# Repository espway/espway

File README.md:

# ESPway
A segway-like balancing two-wheel robot built on ESP8266. It is controlled over WiFi via a HTML/JS GUI and a WebSocket. This is a work in progress. The firmware is meant to run on a WEMOS D1 mini or a similar board.

*NOTE for existing users*: the [Arduino version](https://github.com/flannelhead/espway/tree/arduino) of this code is deprecated and will *not* receive the newest improvements from the main branch. However, the Arduino branch will remain in this repo. If you'd like to have something improved or fixed there, please open an issue or preferably a pull request.

## Getting started
The firmware is built on the [esp-open-rtos](https://github.com/SuperHouse/esp-open-rtos) project which is included as a submodule in this repo.

For building the firmware, a Linux host is recommended. For other platforms, there is a [Docker image](https://hub.docker.com/r/flannelhead/espway-toolchain/) one can use. The `docker-run` script in this repository contains the command that's required to download the image and run commands in the container. It should work fine on macOS hosts. For Windows hosts, I still recommend installing Linux in a virtual machine and installing the tools there.

### Installing the tools and building

*NOTE*: if you intend to use Docker, you only have to install `esptool`, `git` and `make` on your host. Please see below for further Docker instructions.

### Using the Docker image

First, [install Docker](https://www.docker.com/community-edition).

Building the firmware using the supplied Docker image is easy. Instead of running `make parallel`, just run `./docker-run make parallel` in the root folder of the repo. The command supplied to the script will be run in the Docker container, and the image will be automatically downloaded.

Flashing the image differs, though, and for this you'll need `make` on your host. Instead of
```
make flash ESPPORT=/dev/ttyUSBx
```
(`/dev/ttyUSBx` being the ESP's serial port) run
```
make flash-only ESPPORT=/dev/ttyUSBx
```
in your host shell. The separate `flash-only` target is needed because the `flash` target would try to build the firmware. In the future, it is intended to provide a separate Python script for flashing, lifting the need for `make` on host.

*TODO*: `docker-compose` configuration file for even easier usage

### Installing the tools manually (not recommended, not guaranteed to work)

**WARNING**: As of currently, the compiler installed by this method seems to have issues compiling the code. Thus this method is not recommended. Please see above for the Docker-based toolchain instead.

Install these packages:
* `git` (from your package manager)
* `xtensa-lx106-elf` toolchain. You can use `esp-open-sdk` to build it, see the [instructions](https://github.com/SuperHouse/esp-open-rtos/#quick-start) in the esp-open-rtos repo.
* `esptool` (`pip install -U esptool`). Please do not use the outdated version pulled by `esp-open-sdk`.
* `tcc`, `nodejs` and `npm` are currently required due to the frontend code, although I'm investigating how to relax this dependency.

Clone this repo (recursive cloning to get also `esp-open-rtos` and its submodules):
```
git clone --recursive https://github.com/flannelhead/espway.git
```
Enter the directory and build the firmware:
```
make parallel
```
The `parallel` target does a clean build with 5 parallel worker threads to make it faster.

Plug your ESP8266 module in via USB and flash the firmware:
```
make flash
```
The default port is `/dev/ttyUSB0`. If you need to change this, use
```
make flash ESPPORT=/dev/ttyUSBx
```

## Supported browsers
Please use the latest Firefox or Chrome if possible. The HTML/JS UI uses some
recent JavaScript features which might not be supported by older browsers. However if you encounter any issues on e.g. Safari, don't hesitate to file them in the issue tracker.

## Schematic & BOM

There is a PCB design and schematic in the `schematic` folder which has been tested and is ready to use. There, MPU6050 has been replaced by LSM6DS3 and L293D by DRV8835 for better performance.

Meanwhile, you can still build an ESPway using breakout boards available from the usual sources. A rough bill of materials for this is listed below:

* (not including PCB, connectors, wire etc. materials)
* WEMOS D1 Mini board
* GY-521 (MPU6050 breakout board)
* L293D motor driver IC
* 2x 6V 300rpm metal gear motor (search for "12ga 300rpm" or "n20 300rpm"), these should be $3-5 per piece
* 2x WS2812B neopixels for eyes and showing current state
* AMS1117 5V regulator
* 5x 100n ceramic capacitors
* 2x 1000u 10V electrolytic capacitor
* 470 ohm resistor
* 10 kohm resistor
* 680 kohm resistor

To use the old hardware config and schematic, you'll have to edit `src/espway_config.h` before compilation. See that file for notes.

See the `schematic-old` folder for the schematic. It is drawn with [KiCad](https://kicad.org/) and there's a [rendered PDF](https://github.com/flannelhead/espway/raw/master/schematic/espway.pdf) in the repo.

The new schematic in `schematic` folder uses components
from [kicad-ESP8266](https://github.com/jdunmire/kicad-ESP8266) by J. Dunmire,
licensed under CC-BY-SA 4.0. The schematic is also licensed under CC-BY-SA 4.0.

## Developing the frontend
The HTML/JS frontend uses [Webpack](https://webpack.github.io/) as the build system. You will need [NodeJS](https://nodejs.org/en/) and NPM (the package manager) to build the frontend pages. It does jobs like bundling the JavaScript modules together, minifying and transpiling the [ES2015](https://babeljs.io/learn-es2015/) code for older browsers, compiling [Riot tags](https://riot.js.org/), minifying/autoprefixing CSS etc.

After you've cloned this repo, run `npm install` in the root folder to install the package dependencies. There are two commands specified in `package.json` which run Webpack:

* `npm run serve` start a web server which serves the static HTML files in the `frontend/output` directory. It also watches for changes in the source files in `frontend/src` and automatically rebuilds and reloads them. Use this while hacking on the frontend. *TODO*: Currently this doesn't see changes to HTML files, though.
* `npm run build` produces a production build of the frontend JS/CSS bundles. Use this before uploading your work to the ESP8266.

## License and acknowledgements
The project is licensed under LGPLv3.

The project uses `esp-open-rtos` which is licensed under the BSD 3-clause license. It also has some components which have different licenses. Read more about them in the [`esp-open-rtos` README](https://github.com/SuperHouse/esp-open-rtos/blob/master/README.md).

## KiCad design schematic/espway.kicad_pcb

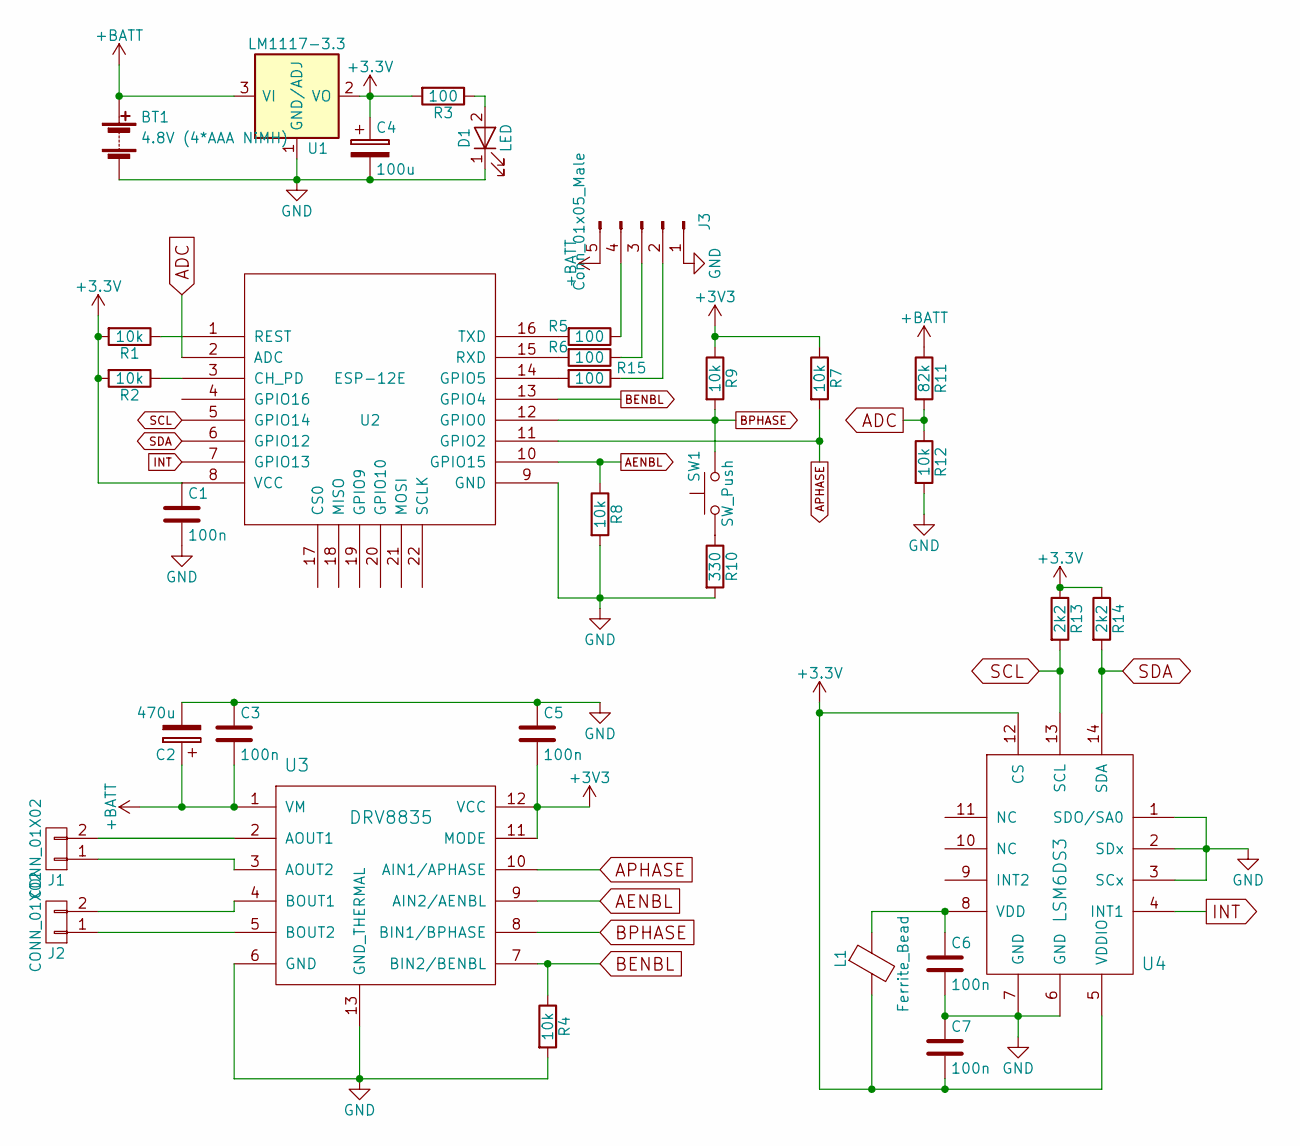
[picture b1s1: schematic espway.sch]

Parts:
BT1: 4.8V (4*AAA NiMH); WireConnection_1.20mmDrill
C1, C3, C5, C6, C7: 100n; C_0603
C2: 470u; CP_Elec_8x10
C4: 100u; CP_Elec_6.3x5.8
D1: LED; LED_0603
J1, J2: CONN_01X02; WireConnection_1.00mmDrill
J3: Conn_01x05_Male; Pin_Header_Angled_1x05_Pitch2.54mm
L1: Ferrite_Bead; L_0603
R1, R2, R4, R7, R8, R9, R12: 10k; R_0603
R3, R5, R6, R15: 100; R_0603
R10: 330; R_0603
R11: 82k; R_0603
R13, R14: 2k2; R_0603
SW1: SW_Push; SW_SPST_KMR2
U1: LM1117-3.3; SOT-223
U2: ESP-12E; ESP-12E_SMD
U3: DRV8835; WSON-12-1EP_3x2mm_Pitch0.5mm_ThermalVias
U4: LSM6DS3; Bosch_LGA-14_3x2.5mm_Pitch0.5mm

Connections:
+BATT: BT1.1 (+), C2.1, C3.2, J3.5, R11.1, U1.3 (VI), U3.1 (VM)
ADC: R11.2, R12.1, U2.2 (ADC)
AENBL: R8.1, U2.10 (GPIO15), U3.9 (AIN2/AENBL)
APHASE: R7.2, U2.11 (GPIO2), U3.10 (AIN1/APHASE)
BENBL: R4.1, U2.13 (GPIO4), U3.7 (BIN2/BENBL)
BPHASE: R9.2, SW1.2, U2.12 (GPIO0), U3.8 (BIN1/BPHASE)
GND: BT1.2 (-), C1.2, C2.2, C3.1, C4.2, C5.1, C6.2, C7.1, D1.1 (K), J3.1, R4.2, R8.2, R10.2, R12.2, U1.1 (GND/ADJ), U2.9 (GND), U3.6 (GND), U3.13 (GND_THERMAL), U4.1 (SDO/SA0), U4.2 (SDx), U4.3 (SCx), U4.6 (GND), U4.7 (GND)
INT: U2.7 (GPIO13), U4.4 (INT1)
unnamed: C6.1, L1.1, U4.8 (VDD)
unnamed: D1.2 (A), R3.1
unnamed: J1.1, U3.3 (AOUT2)
unnamed: J1.2, U3.2 (AOUT1)
unnamed: J2.1, U3.5 (BOUT2)
unnamed: J2.2, U3.4 (BOUT1)
unnamed: J3.2, R15.1
unnamed: J3.3, R6.1
unnamed: J3.4, R5.1
unnamed: R1.1, U2.1 (REST)
unnamed: R2.1, U2.3 (CH_PD)
unnamed: R5.2, U2.16 (TXD)
unnamed: R6.2, U2.15 (RXD)
unnamed: R10.1, SW1.1
unnamed: R15.2, U2.14 (GPIO5)
SCL: R13.2, U2.5 (GPIO14), U4.13 (SCL)
SDA: R14.2, U2.6 (GPIO12), U4.14 (SDA)

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
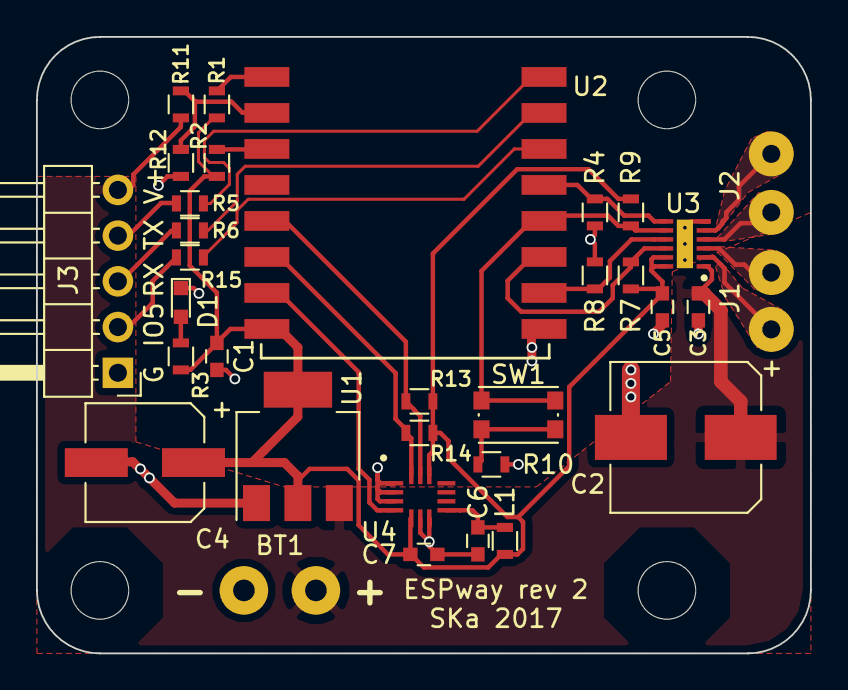
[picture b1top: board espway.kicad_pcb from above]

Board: 2 copper layers, 43.0 x 34.2 mm, 33 parts (0 on the bottom side), 26 nets.

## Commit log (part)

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2016-12-07 Some improvements to server
2016-12-07 Revise Content-Type, RODATA access
2016-12-07 Minor fixes
2016-12-07 Now able to send large files
2016-12-07 Add user-scalable=no
2016-12-09 Remove libesphttpd
2016-12-10 HTTP clients now handled individually
2016-12-10 Add SHA1 from mbedtls
2016-12-10 Add base64 and sha1 from Brad Conte
2016-12-10 Refactor websock parsing & add more checks
2016-12-10 Refactor even more
2016-12-10 Websocket handshake works
2016-12-10 Handling of binary and text data for WS
2016-12-10 Don't disconnect from websocket
2016-12-10 Remove driver_store
2016-12-10 Move files from driver to lib
2016-12-10 Websocket sending
2016-12-10 LOCAL -> static, fix a typo
2016-12-10 Use the stored espconn pointer for sending
2016-12-10 Move some stuff to header
2016-12-10 Implement websocked_send_all
2016-12-12 Fix a couple of websocket things
2016-12-12 Websocket working somewhat well
2016-12-12 Cleanups
2016-12-12 Use the websocket callback
2016-12-12 Fix websocket send
2016-12-12 Wire in the websocket communication in user_main
2016-12-12 Yay, websocket quaternion works now!
2016-12-14 Start porting MadgwickAHRS to fixed point
2016-12-15 Fixed point Madgwick almost works now
2016-12-17 Frequency counting, improvements
2016-12-17 Avoid needless scaling of quaternion
2016-12-22 Hopefully rest of motor driver
2017-02-04 Rebooting project with NONOS SDK
2017-02-04 Serving files now works
2017-02-04 I2C somewhat working
    Add config
    Add ICACHE_FLASH_ATTR modifiers to library functions
2017-02-05 Improve & clean up I2C driver
2017-02-05 Add most of the original code
2017-02-05 Add in the websocket functions
2017-02-05 Implement motor drive
2017-02-05 Small changes to make OTA update work
2017-02-05 Implement eyes control
2017-02-05 Eyes & motors handling on OTA
2017-02-05 Mention Riot.js
2017-02-05 Remove src folder
2017-02-05 GPLv3 headers
2017-02-06 Remove old TODO
2017-02-06 Add flash_config functions
2017-02-07 PID config get/set on backend
2017-02-08 Explicitly set softap IP
2017-02-08 Make battery cutoff separately configurable
2017-02-08 Fix PID initialization
2017-02-08 Add BOM to README
2017-02-09 Bugfixes to websocket communication
2017-02-10 Immediately schedule new computation call
2017-02-10 Fixes to PID live tuning
2017-02-11 brzo_i2c: don't disable interrupts, reduce clock stretch timeout
2017-02-11 Fix typo
2017-02-11 Explicitly set all of the softap config
2017-02-11 Implement REQ_DEFAULT_PID_PARAMS
    Refactor default configuration
2017-02-11 Refactor to use pid_coeffs more extensively
2017-02-11 Implement loading hardcoded PID defaults
2017-02-11 Pretty pring current config on boot
2017-02-13 Transform build process to webpack [WIP]
2017-02-13 Changes to module dependencies
2017-02-13 Add custom riot-loader
2017-02-13 Fix rest of css & bundle imports
2017-02-13 PID UI: attach message handler before opening websocket
2017-02-15 Add useful build commands and setup dev server
2017-02-15 Stylize the PID tuning page a bit
2017-02-18 Automatic updating of the high gain PID
2017-02-18 Replace PID select with radio buttons
2017-02-18 Update README regarding Webpack
2017-02-18 Reorganize README, add TODO list
2017-02-18 Increase clock stretch timeout
2017-03-31 Adjust makefiles
2017-03-31 Update brzo_i2c
2017-04-01 Fix eyes color
2017-04-03 Begin porting back to Arduino [WIP]
2017-04-04 Call SPIFFS.begin
2017-04-04 Fix bug in flash_config
2017-04-04 Small fixes
2017-04-04 Don't use NMI
    minor adjustments
2017-04-04 Enable OTA updating
2017-04-04 Fix reading the interrupt status
2017-04-04 Add aliases for pages
2017-04-04 Fall detection works sideways
2017-04-05 Motor speed "wind-up" prevention
2017-04-07 Const correctness in flash_config
2017-04-17 Serve webpack files on 0.0.0.0
2017-04-17 Fix touch actions
2017-04-17 Fix multitouch confusion
2017-04-17 More backwards compatibility
2017-05-25 Use location.hostname for the websocket url
2017-05-25 Disable chrome pull-to-refresh through JavaScript
2017-05-25 Restructure source files, add local brzo_i2c
2017-05-25 Fix README
2017-06-15 Add esp-open-rtos as a submodule
2017-06-15 Add example softap script
2017-06-20 Add flash target to makefile
2017-06-20 Remove fsdata.c from repo
2017-06-21 Start working on i2c and MPU
2017-06-26 Port a lot more stuff over
2017-06-27 Implement battery logging
2017-06-28 Log pitch
2017-06-29 Fix one issue with semaphores
2017-07-10 Increase main loop priority, fix sysparam mistakes
2017-07-20 Revise local make flags
2017-07-24 Update esp-open-rtos
2017-07-24 Fixes and cleanups to PWM driver
2017-07-24 Make PWM period configurable
    Fixes to logging in main thread
2017-07-24 Cleanup: remove lib-store
    Everything has been ported over
2017-07-24 Add KDevelop project
2017-07-25 Add captive DNS from libesphttpd
2017-07-25 Add custom dhcpserver.h
2017-07-25 Switch to espway-devel branch of esp-open-rtos
2017-07-25 Enable CGIs and add shorthands for cube and pid pages
2017-07-26 Replace captdns with dnsresponder
2017-07-26 Add handlers for steering and IMU timeouts
2017-07-29 Add new IMU filter
2017-07-29 Add tilt display to control UI
2017-07-30 Add Mahony filter and use it by default
    Adjustments and improvements to q16 and vector calculations.
    Other filters will probably be eventually removed.
2017-08-01 Split espway.cpp into smaller files
2017-08-01 A tad better file structure
2017-08-06 Add esp-open-sdk as a subproject
2017-08-07 Remove the KDevelop files
2017-08-10 Add ctags "tags" file to .gitignore
2017-08-10 Style: braces on their own lines
2017-08-11 Add a simple hardfault handler
2017-08-15 Makefile: use rebuild target instead of all
2017-08-15 Apply patches from ourairquality
    https://github.com/SuperHouse/esp-open-rtos/pull/437
2017-08-17 Update esp-open-rtos, other small changes
2017-08-17 Rename html-src to src
2017-08-29 Some debugging related changes
2017-08-30 A working version with new LwIP
2017-09-01 Enable IMU timeout watcher
2017-09-01 Adjust some config settings
2017-09-01 Remove DNS responder, set default IP to 10.0.0.1
2017-09-01 Adjust IMU filter params
2017-09-01 Remove esp-open-sdk submodule
    It probably isn't going to be very useful as is. A Docker image will be
    considered.
2017-09-01 Remove leftover files from html folder
2017-09-01 Restructuring of ESPway cpp files
2017-09-01 Fix Makefile errors
2017-09-01 Disable send_gravity for now
2017-09-04 Update to newer lwIP revision
2017-09-09 Include fsdata.c in repo
2017-09-12 Fix Makefile dependency of src/fsdata.c
2017-09-14 Add kicad net file, begin associating footprints
2017-09-14 Updates to schematic
2017-09-17 Ignore KiCAD PCB backup files
2017-09-17 Schematic and PCB update
2017-09-19 Update PCB
2017-09-19 Add debug output for brzo_i2c mpu6050 init
2017-09-23 Remove ANGLE_HIGH coefficients from config.h
2017-09-23 Add support for DRV8835 motor driver
2017-09-27 Begin work on IMU HAL
2017-09-28 I2C changes finished
2017-09-28 esp-open-rtos: track espway-devel branch
2017-10-01 Disable ooseq queueing and sack
    These seem to cause some latency for reasons currently unknown
2017-10-12 Rename MPU_ADDR -> IMU_ADDR
2017-10-12 Start LSM6DS3 driver, fix config.h mess
2017-10-12 LSM6DS3 driver working
2017-10-13 Prevent warning about missing include
2017-10-14 motors.c bugfixes
2017-10-14 Multiple fixes and config improvements
2017-10-14 Makefile: add just-flash target
2017-10-14 Update frontend
2017-10-14 Tuning parameters
2017-10-14 Enable sending gravity vector
2017-10-15 Back to 1.66 kHz ODR
2017-10-15 Plenty of updates to PCB
    * Fix bug where one motor would spin in bootloader
    * Add helpful labels
    * Add another via for V+ near motor driver
    * Larger screw holes
2017-10-15 Ignore .DS_Store
2017-10-16 Ignore plot files in schematic folder
2017-10-16 Config adjustments
    Minor shuffling around in imu_i2c_helper
2017-10-16 Add upstream brzo_i2c
    This commit won't build - the library needs adaptation
2017-10-16 brzo_i2c: adapt to esp-open-rtos
2017-10-16 Use 80 MHz clock
2017-10-16 Robustness against I2C errors
2017-10-16 Remove useless intermediate buffer
2017-10-16 Make motor pins configurable
2017-10-18 Tune PWM for 160 MHz CPU freq
2017-10-18 Main file cleanup
2017-10-24 Add pwm library license
2017-11-02 Fixes to LUT generation script
2017-11-02 Add comments to q16_rsqrt
2017-11-28 PCB update before rerouting
2017-11-29 Initial work on new PCB
2017-12-01 An intermediate commit
2017-12-01 Clarify modifications in pwm.c
2017-12-03 PCB: stable checkpoint
2017-12-03 PCB adjustments
2017-12-04 Drop brzo_i2c in favour of esp-open-rtos builtin driver
2017-12-08 Update esp-open-rtos, change I2C IMU API
2017-12-09 Port C++ code to C
2017-12-09 Makefile: generate single binary
    Set ENABLE_CXX = 0
2017-12-10 lib: declare inline functions static
2017-12-10 Makefile: set ENABLE_CXX = 0
2017-12-10 espway_config.cpp: add missing include
2017-12-12 Replace ESP8266_new_pwm with delta-sigma modulator
2017-12-12 .gitignore .vscode
2017-12-13 delta_sigma: add a couple of domain checks
2017-12-13 Fix Makefile issues
2017-12-13 Makefile: use tcc instead of gcc
2017-12-18 Remove unndeeded ENABLE_CXX flag
2017-12-20 motors.c: adjust delta-sigma period
2017-12-20 espway_server: small improvements
2017-12-21 Makefile: manually specify flash params
2017-12-21 Increase flash size
    ESP-12S modules have 4 MB of flash
2017-12-26 Schematic: change resistor values, break out extra GPIO pin
2017-12-27 schematic & pcb: pullup fixes etc
2017-12-27 Minor PCB track adjustments
2018-01-01 Final changes to schematic
2018-01-15 Add IMU interrupt pin definition, document more parameters
2018-01-15 Updates to README and schematics
2018-01-19 Fix some mistakes preventing compilation
2018-01-23 Adaptation for new PCB
2018-01-23 Minor component value updates
2018-01-23 Add notes about new schematic
2018-01-23 vector3d_fix: better interface
2018-01-23 Saner battery scaling
2018-01-23 LF line endings
2018-01-23 Minor styling
2018-01-31 delta-sigma: use taskENTER_CRITICAL and taskEXIT_CRITICAL
2018-02-01 Add foundations for maze solver
    Revert the GPIO handler change - it is already handled by esp-open-rtos
2018-02-03 ultrasonic: increase reliability, remove some race conditions
2018-02-04 Allow synchronized access to steering from outside
2018-02-04 Improve handling of orientation
2018-02-05 delta_sigma: use interrupt safe critical section entry/exit
2018-02-06 Working toward maze solving
2018-02-13 Add .clang_complete file
2018-02-13 Maze pinging now working
2018-02-19 Disable maze solving by default
2018-02-25 Add and use RAII locking mechanisms
2018-02-25 Implement probing for ultrasonic sensors and initiate maze solving
2018-02-25 samplebuffer: add reset function
2018-02-25 Fixes to wall follower logic
2018-02-28 Move color constants to eyes module
2018-02-28 ultrasonic: remove unnecessary delay
2018-02-28 Maze solver: logic fixes
2018-03-01 ultrasonic: perform triggering inside critical section
    Decrease trigger pulse width
2018-03-02 Better tunings and minor fixes
2018-10-18 Add beginnings of Elm GUI
2019-05-28 Update esp-open-rtos submodule
2019-06-10 Makefile: remove dependency on the frontend sources
    Frontend builds are managed separately by the NPM package.json and
    friends.
2019-06-10 Makefile: document where the other "all" dependencies come from
2019-10-31 Bump webpack-dev-server from 2.3.0 to 3.1.11 in /frontend
    Bumps [webpack-dev-server](https://github.com/webpack/webpack-dev-server) from 2.3.0 to 3.1.11.
    - [Release notes](https://github.com/webpack/webpack-dev-server/releases)
    - [Changelog](https://github.com/webpack/webpack-dev-server/blob/master/CHANGELOG.md)
    - [Commits](https://github.com/webpack/webpack-dev-server/compare/v2.3.0...v3.1.11)
2019-12-23 Specify correct license in package.json
2019-12-23 Set "private": true in package.json
